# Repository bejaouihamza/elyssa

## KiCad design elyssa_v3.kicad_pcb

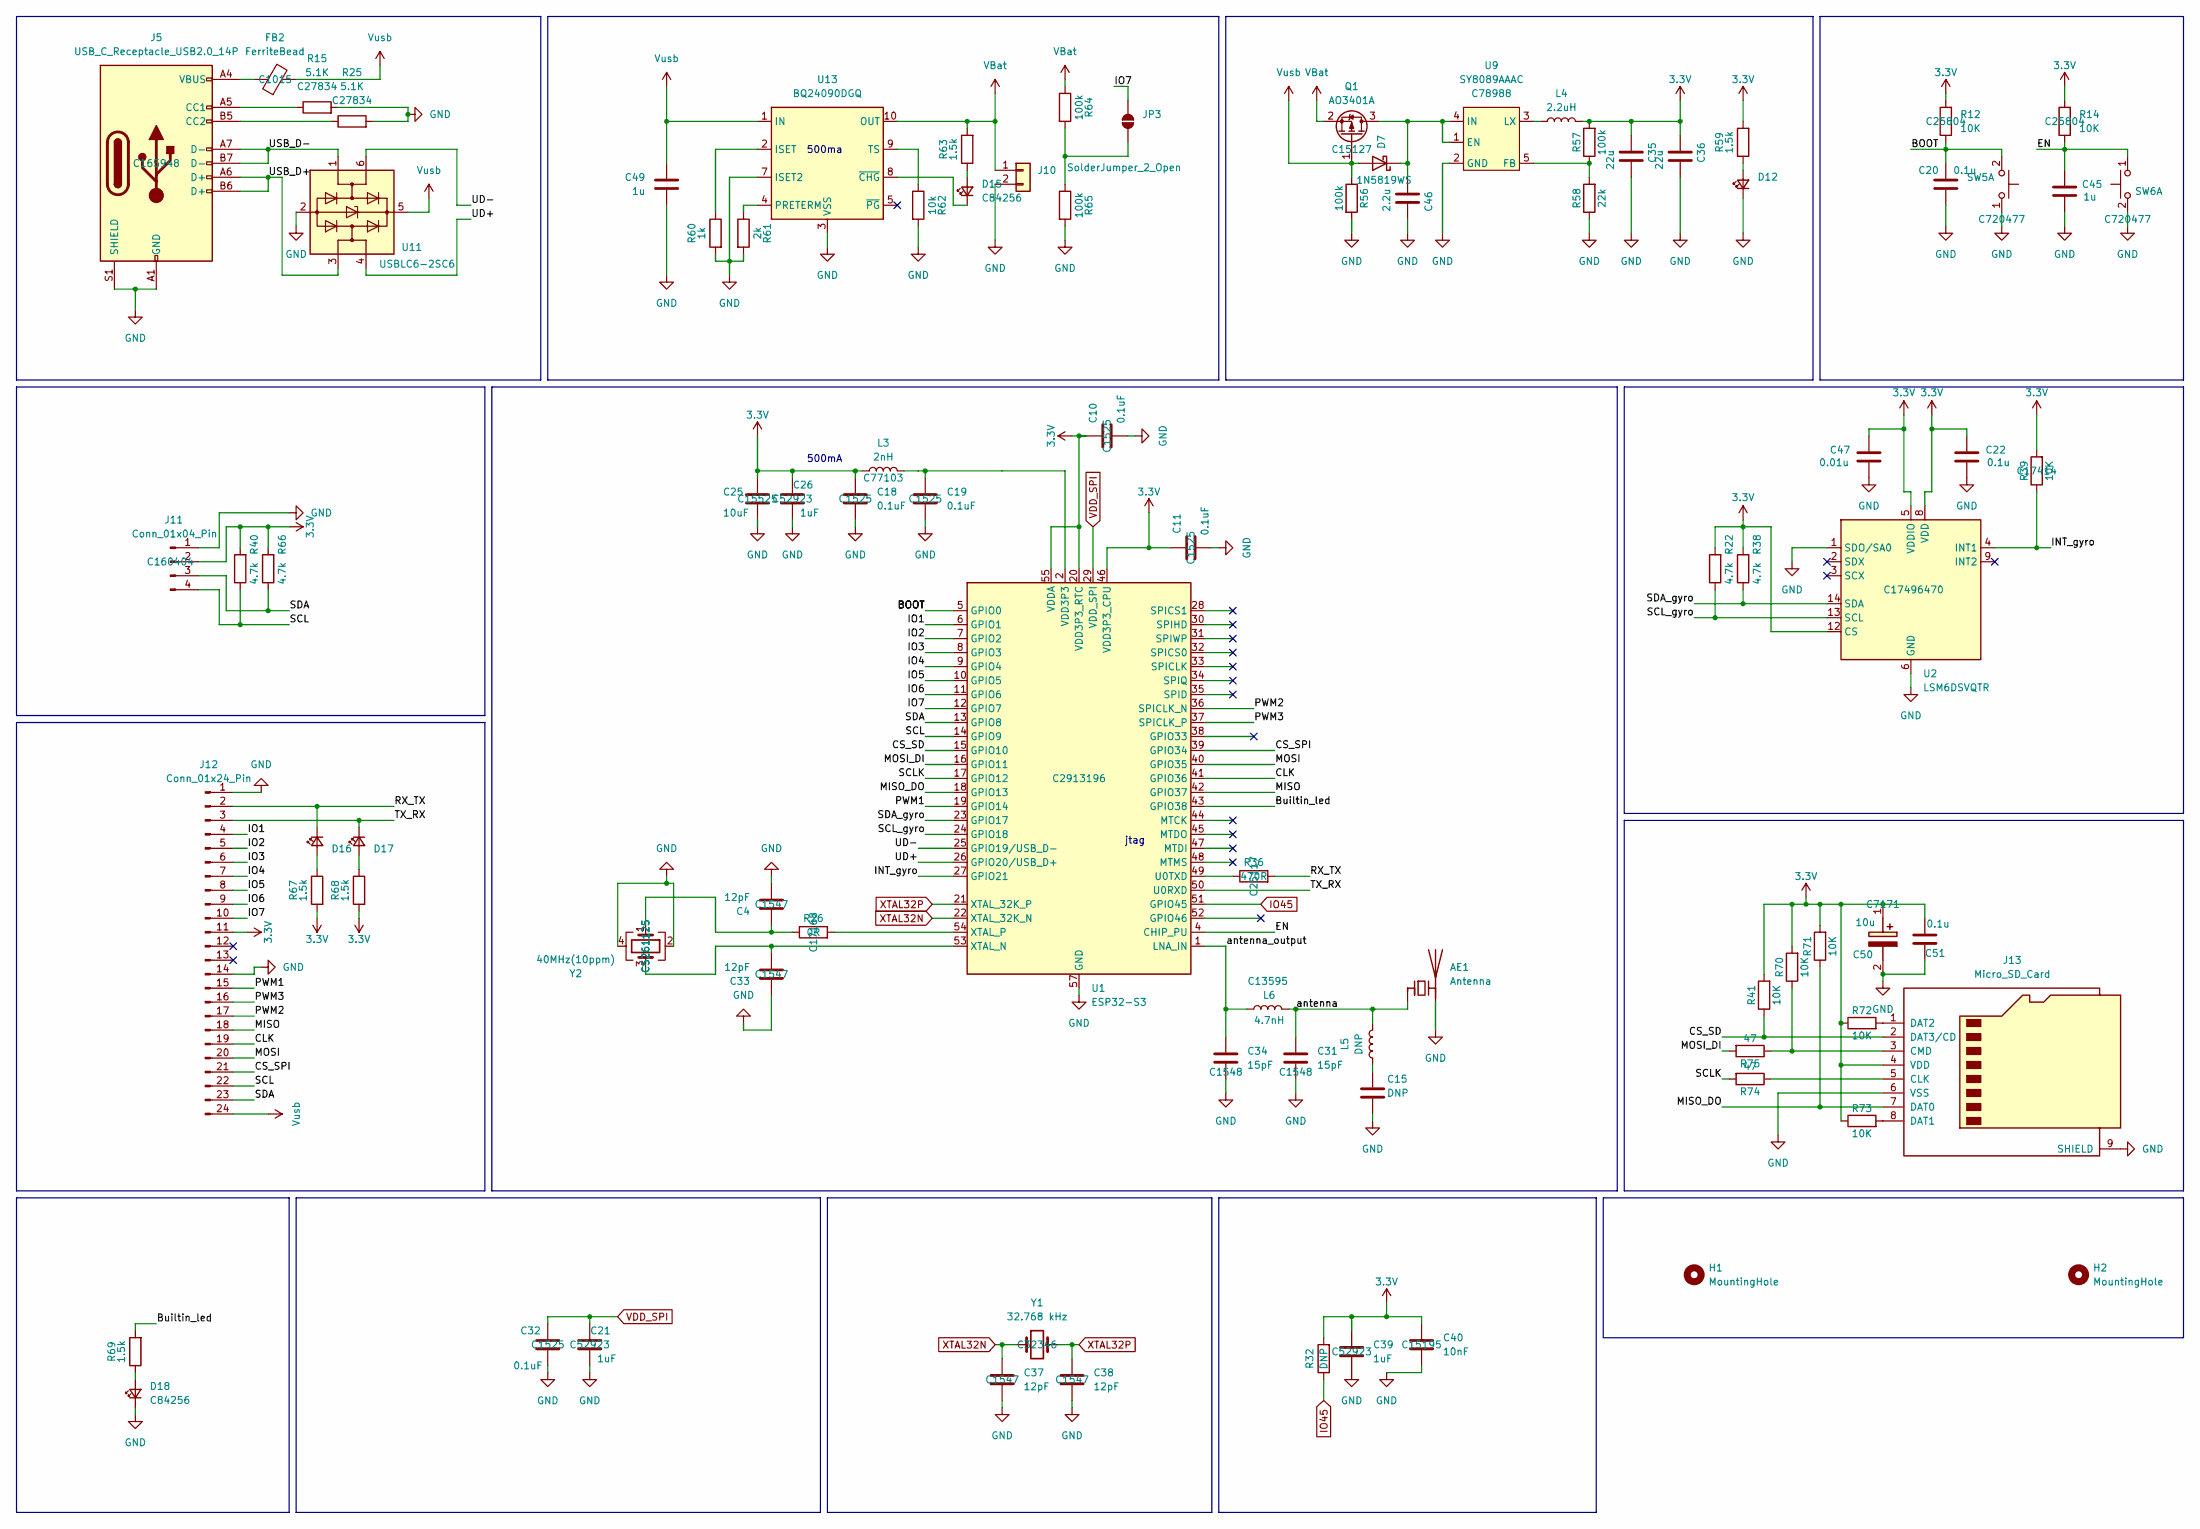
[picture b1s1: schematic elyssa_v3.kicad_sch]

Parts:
AE1: Antenna; Texas_SWRA117D_2.4GHz_Left
C4, C33, C37, C38: 12pF; C_0402_1005Metric; MNF PART NUMBER C1547; LCSC Part # C1547
C10, C11, C18, C19, C32: 0.1uF; C_0402_1005Metric; MNF PART NUMBER C1525; LCSC Part # C1525
C15: DNP; C_0402_1005Metric
C20, C22: 0.1u; C_0603_1608Metric; Voltage 1kV; Tolerance 100%
C21, C26, C39: 1uF; C_0402_1005Metric; MNF PART NUMBER C52923; LCSC Part # C52923
C25: 10uF; C_0402_1005Metric; MNF PART NUMBER C15525; LCSC Part # C15525
C31, C34: 15pF; C_0402_1005Metric; MNF PART NUMBER C1548; LCSC Part # C1548
C35, C36: 22u; C_0805_2012Metric; Voltage 1kV; Tolerance 100%
C40: 10nF; C_0402_1005Metric; MNF PART NUMBER C15195; LCSC Part # C15195
C45: 1u; C_0603_1608Metric; Voltage 1kV; Tolerance 100%
C46: 2.2u; R_0805_2012Metric; Voltage 1kV; Tolerance 100%
C47: 0.01u; C_0603_1608Metric; Voltage 1kV; Tolerance 100%
C49: 1u; C_0603_1608Metric
C50: 10u; CP_EIA-3216-18_Kemet-A; Voltage 1kV; Tolerance 100%; Manufacturer_Part_Number T491A106K010AT7280; Mouser Part Number 80-T491A106K107280
C51: 0.1u; C_0805_2012Metric; Voltage 1kV; Tolerance 100%
D7: 1N5819WS; D_SOD-323
D12: LED_Small; LED_0805_2012Metric; LCSC Part # C2297
D15, D18: LED_Small; LED_0805_2012Metric; LCSC Part # C84256
D16, D17: LED_Small; LED_0805_2012Metric; LCSC Part # C2296
FB2: FerriteBead; L_0805_2012Metric; LCSC Part # C1015
H1, H2: MountingHole; MountingHole_2.1mm_Pade
J5: USB_C_Receptacle_USB2.0_14P; USB_C_Receptacle_HRO_TYPE-C-31-M-12; LCSC Part # C165948
J10: Conn_01x02; JST_PH_S2B-PH-K_1x02_P2.00mm_Horizontal
J11: Conn_01x04_Pin; JST_SH_SM04B-SRSS-TB_1x04-1MP_P1.00mm_Horizontal; LCSC Part # C160404
J12: Conn_01x24_Pin; Molex_SL_171971-0024_1x24_P2.54mm_Vertical
J13: Micro_SD_Card; TF-01A
JP3: SolderJumper_2_Open; SolderJumper-2_P1.3mm_Open_RoundedPad1.0x1.5mm
L3: 2nH; L_0402_1005Metric; MNF PART NUMBER C77103; LCSC Part # C77103
L4: 2.2uH; L_1210_3225Metric
L5: DNP; L_0402_1005Metric
L6: 4.7nH; L_0402_1005Metric; MNF PART NUMBER C13595; LCSC Part # C13595
Q1: AO3401A; SOT-23; LCSC Part # C15127
R12, R14, R72: 10K; R_0603_1608Metric; LCSC Part # C25804
R15, R25: 5.1K; R_0805_2012Metric; LCSC Part # C27834
R22, R38: 4.7k; R_0603_1608Metric
R26: 0R; R_0402_1005Metric; MNF PART NUMBER C17168; LCSC Part # C17168
R32: DNP; R_0402_1005Metric
R36: 470R; R_0402_1005Metric; MNF PART NUMBER C25117; LCSC Part # C25117
R39: 10K; R_0603_1608Metric; LCSC Part # C17414
R40, R66: 4.7k; R_0805_2012Metric
R41, R70, R71, R73: 10K; R_0603_1608Metric
R56, R64, R65: 100k; R_0805_2012Metric
R57: 100k; R_0603_1608Metric
R58: 22k; R_0603_1608Metric; LCSC Part # C31850
R59, R63, R67, R68, R69: 1.5k; R_0402_1005Metric
R60: 1k; R_0402_1005Metric
R61: 2k; R_0402_1005Metric
R62: 10k; R_0805_2012Metric
R74, R75: 47; R_0402_1005Metric
SW5, SW6: SW_Push_Dual_x2; SW_TS-1088-AR02016; LCSC Part # C720477
U1: ESP32-S3; QFN-56-1EP_7x7mm_P0.4mm_EP4x4mm; MNF PART NUMBER C2913196
U2: LSM6DSVQTR; LGA-14_3x2.5mm_P0.5mm_LayoutBorder3x4y; LCSC Part # C17496470
U9: SY8089AAAC; SOT-23-5; LCSC Part# C78988
U11: USBLC6-2SC6; SOT-23-6; Manufacturer_Part_Number USBLC6-2SC6; Mouser Part Number 511-USBLC6-2SC6
U13: BQ24090DGQ; HVSSOP-10-1EP_3x3mm_P0.5mm_EP1.57x1.88mm_ThermalVias
Y1: 32.768 kHz; Crystal_SMD_3215-2Pin_3.2x1.5mm; MNF PART NUMBER C32346; LCSC Part # C32346
Y2: 40MHz(10ppm); Crystal_SMD_2520-4Pin_2.5x2.0mm; MNF PART NUMBER C5261125; LCSC Part # C5261125

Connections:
3.3V: C10.1, C11.1, C18.1, C22.1, C25.1, C26.1, C35.1, C36.1, C39.1, C40.1, C47.1, C50.1 (+), C51.2, J11.2, J12.11, J13.4 (VDD), L3.1, L4.2, R12.2, R14.2, R22.2, R32.2, R38.2, R39.2, R40.2, R41.2, R57.2, R59.2, R66.2, R67.2, R68.2, R70.2, R71.2, R72.1, R73.1, U1.20 (VDD3P3_RTC), U1.46 (VDD3P3_CPU), U1.55 (VDDA), U1.56 (VDDA), U2.5 (VDDIO), U2.8 (VDD), U2.12 (CS)
/BOOT: C20.1, R12.1, SW5.2 (D), U1.5 (GPIO0)
/Builtin_led: R69.2, U1.43 (GPIO38)
/CLK: J12.19, U1.41 (GPIO36)
/CS_SD: J13.2 (DAT3/CD), R41.1, U1.15 (GPIO10)
/CS_SPI: J12.21, U1.39 (GPIO34)
/EN: C45.1, R14.1, SW6.1 (C), U1.4 (CHIP_PU)
/INT_gyro: R39.1, U1.27 (GPIO21), U2.4 (INT1)
/IO1: J12.4, U1.6 (GPIO1)
/IO2: J12.5, U1.7 (GPIO2)
/IO3: J12.6, U1.8 (GPIO3)
/IO4: J12.7, U1.9 (GPIO4)
/IO5: J12.8, U1.10 (GPIO5)
/IO6: J12.9, U1.11 (GPIO6)
/IO7: J12.10, JP3.1 (A), U1.12 (GPIO7)
/MISO: J12.18, U1.42 (GPIO37)
/MISO_DO: J13.7 (DAT0), R71.1, U1.18 (GPIO13)
/MOSI: J12.20, U1.40 (GPIO35)
/MOSI_DI: R75.2, U1.16 (GPIO11)
/PWM1: J12.15, U1.19 (GPIO14)
/PWM2: J12.17, U1.36 (SPICLK_N)
/PWM3: J12.16, U1.37 (SPICLK_P)
/RX_TX: D16.1 (K), J12.2, R36.2
/SCL: J11.4, J12.22, R40.1, U1.14 (GPIO9)
/SCLK: R74.2, U1.17 (GPIO12)
/SCL_gyro: R22.1, U1.24 (GPIO18), U2.13 (SCL)
/SDA: J11.3, J12.23, R66.1, U1.13 (GPIO8)
/SDA_gyro: R38.1, U1.23 (GPIO17), U2.14 (SDA)
/TX_RX: D17.1 (K), J12.3, U1.50 (U0RXD)
/UD+: U1.26 (GPIO20/USB_D+), U11.4 (I/O2)
/UD-: U1.25 (GPIO19/USB_D-), U11.6 (I/O1)
/USB_D+: J5.A6 (D+), J5.B6 (D+), U11.3 (I/O2)
/USB_D-: J5.A7 (D-), J5.B7 (D-), U11.1 (I/O1)
/antenna: AE1.1 (FEED), C31.1, L5.2, L6.2
/antenna_output: C34.1, L6.1, U1.1 (LNA_IN)
GND: AE1.2 (PCB_Trace), C4.2, C10.2, C11.2, C15.2, C18.2, C19.2, C20.2, C21.2, C22.2, C25.2, C26.2, C31.2, C32.2, C33.1, C34.2, C35.2, C36.2, C37.2, C38.2, C39.2, C40.2, C45.2, C46.2, C47.2, C49.2, C50.2 (-), C51.1, D12.1 (K), D18.1 (K), J5.A1 (GND), J5.A12 (GND), J5.B1 (GND), J5.B12 (GND), J5.S1 (SHIELD), J10.2, J11.1, J12.1, J12.14, J13.6 (VSS), J13.9 (SHIELD), R15.2, R25.2, R56.2, R58.1, R60.2, R61.2, R62.2, R65.2, SW5.1 (C), SW6.2 (D), U1.57 (GND), U2.1 (SDO/SA0), U2.6 (GND), U2.7 (GND), U9.2 (GND), U11.2 (GND), U13.3 (VSS), U13.7 (ISET2), U13.11 (VSS), Y2.2, Y2.4
IO45: R32.1, U1.51 (GPIO45)
unnamed: C4.1, R26.1, Y2.1
unnamed: C15.1, L5.1
unnamed: C19.1, L3.2, U1.2 (VDD3P3), U1.3 (VDD3P3)
unnamed: C46.1, D7.1 (K), Q1.3 (D), U9.1 (EN), U9.4 (IN)
unnamed: D12.2 (A), R59.1
unnamed: D15.2 (A), R63.1
unnamed: D15.1 (K), U13.8 (~CHG)
unnamed: D16.2 (A), R67.1
unnamed: D17.2 (A), R68.1
unnamed: D18.2 (A), R69.1
unnamed: FB2.1, J5.A4 (VBUS), J5.A9 (VBUS), J5.B4 (VBUS), J5.B9 (VBUS)
unnamed: J5.A5 (CC1), R15.1
unnamed: J5.B5 (CC2), R25.1
unnamed: J13.5 (CLK), R74.1
unnamed: J13.3 (CMD), R70.1, R75.1
unnamed: J13.8 (DAT1), R73.2
unnamed: J13.1 (DAT2), R72.2
unnamed: JP3.2 (B), R64.2, R65.1
unnamed: R36.1, U1.49 (U0TXD)
unnamed: C33.2, U1.53 (XTAL_N), Y2.3
unnamed: R26.2, U1.54 (XTAL_P)
unnamed: R57.1, R58.2, U9.5 (FB)
unnamed: L4.1, U9.3 (LX)
unnamed: R60.1, U13.2 (ISET)
unnamed: R61.1, U13.4 (PRETERM)
unnamed: R62.1, U13.9 (TS)
VBat: J10.1, Q1.2 (S), R63.2, R64.1, U13.10 (OUT)
VDD_SPI: C21.1, C32.1, U1.29 (VDD_SPI)
Vusb: C49.1, D7.2 (A), FB2.2, J12.24, Q1.1 (G), R56.1, U11.5 (VBUS), U13.1 (IN)
XTAL32N: C37.1, U1.22 (XTAL_32K_N), Y1.1
XTAL32P: C38.1, U1.21 (XTAL_32K_P), Y1.2

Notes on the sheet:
jtag
500ma
500mA

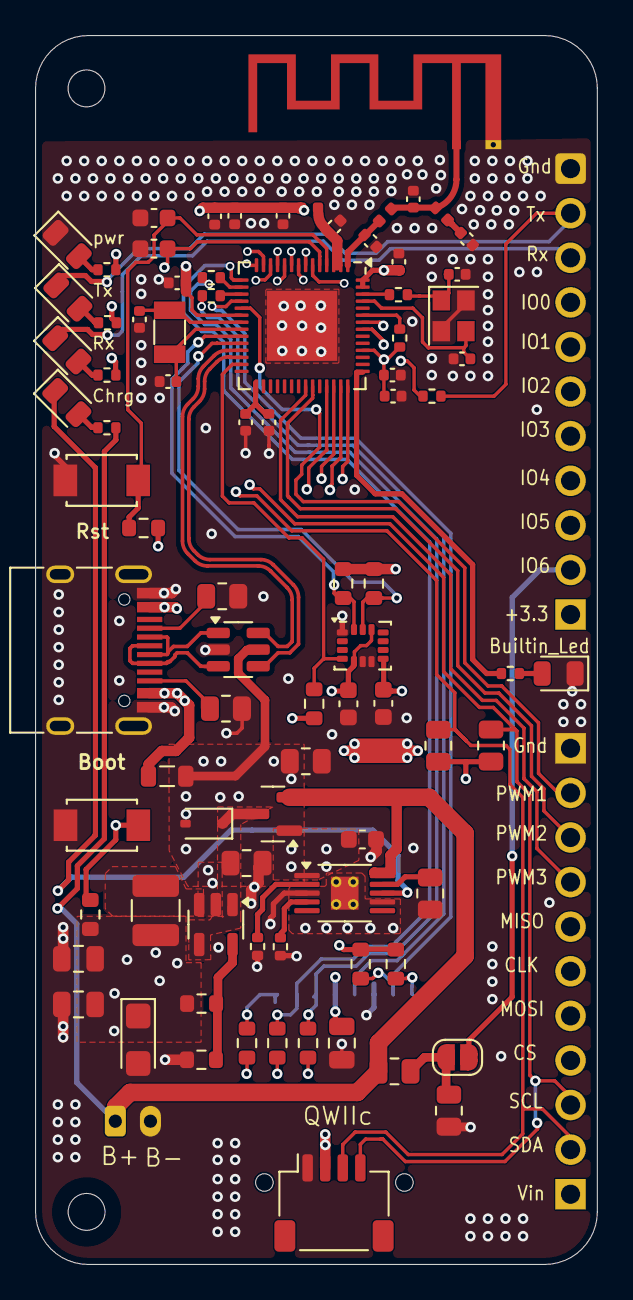
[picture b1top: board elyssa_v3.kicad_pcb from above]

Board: 4 copper layers, 32.0 x 70.0 mm, 89 parts (1 on the bottom side), 68 nets.

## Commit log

2026-04-18 Update print statement from 'Hello' to 'Goodbye'
